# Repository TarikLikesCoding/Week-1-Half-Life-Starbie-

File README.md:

# Week-1-Half-Life-Starbie
Learning PCB's through Hack Club's Half Life program, currently working on week 1.

# What is it?
The Starbie I made is a little robot pet that you can carry anywhere. It has a lithium 3.7V battery that can be recharged. The Starbie is a robot pet with visuals on it small OLED screen, and can be interacted with using the two buttons on it and by motion of the pet. I made it with the purpose of learning how to make PCB's and made it truly mine by exploring convenience features like mobility and rechargability of it.

# How does it work?
My Starbie comes with two buttons that are used to move through the menu and interact with the actual pet inside my Starbie. There is an OLED to see the Starbie reacting to my inputs and give visuals to the project. There is a XIAO ESP32 that does all the processing in a compact chip. There are other components such as MPU-6050 and DHX711 to give the Starbie features like temperature sensing and overall motion sensing. It has a battery charging module and a LiPo battery to run when the Starbie is not connected to the laptop.

# Some Pictures

Schematic

PCB

| Part | Qty | Unit | Total | Vendor | Notes |
| :--- | :---: | :---: | :---: | :--- | :--- |
| **0.96 inch OLED Display Module** with Protector Case 128x64 SSD1306 Screen Board with 4 Pins Soldered Work Great for Arduin | 1 | $5.60 | $5.60 | Amazon | The screen that shows my starbie |
| **10PCS Blue Mechanical Keyboard Switches**, 3 Pin Clickers for Gaming | 4 | $0.48 | $1.92 | Amazon | The buttons on my starbie |
| **TP4056 Type-c USB 5V 1A 18650 Lithium Battery Charger Module** Charging Board with Dual Protection Functions 3PCS | 1 | $6.66 | $6.66 | Amazon | The charging of my LiPo battery |
| **Chanzon SPDT Mini Micro Slide Switch** 1p2t 2 Position 20pcs 3mm Toggle Vertical Slide Switch Panel Mount Small High Knob | 2 | $0.25 | $0.50 | Amazon | The switch to turn on/off the battery when the project is connected to my computer |
| **EEMB 3.7V Li-ion 502030 Battery** 250mAh Lipo Battery Rechargeable Lithium Polymer ion Battery Pack with JST Connector. | 1 | $11.91 | $11.91 | Amazon | The battery thats going to be running my starbie even without my laptop |
| **MiiEIAOD XIAO ESP32C3 Mini IoT Board** with High-Performance Cost-Effective Wi-Fi/Ble (1PCS Kit)MiiEIAOD XIAO ESP32C3 Min | 1 | $10.10 | $10.10 | Amazon | The actual brain behind my starbie |
| **PCB** | 1 | $20.55 | $20.55 | JLCPCB | The skeleton of what I will be building on |
| **Tax & shipping** | - | - | $7.44 | - | For the whole order |

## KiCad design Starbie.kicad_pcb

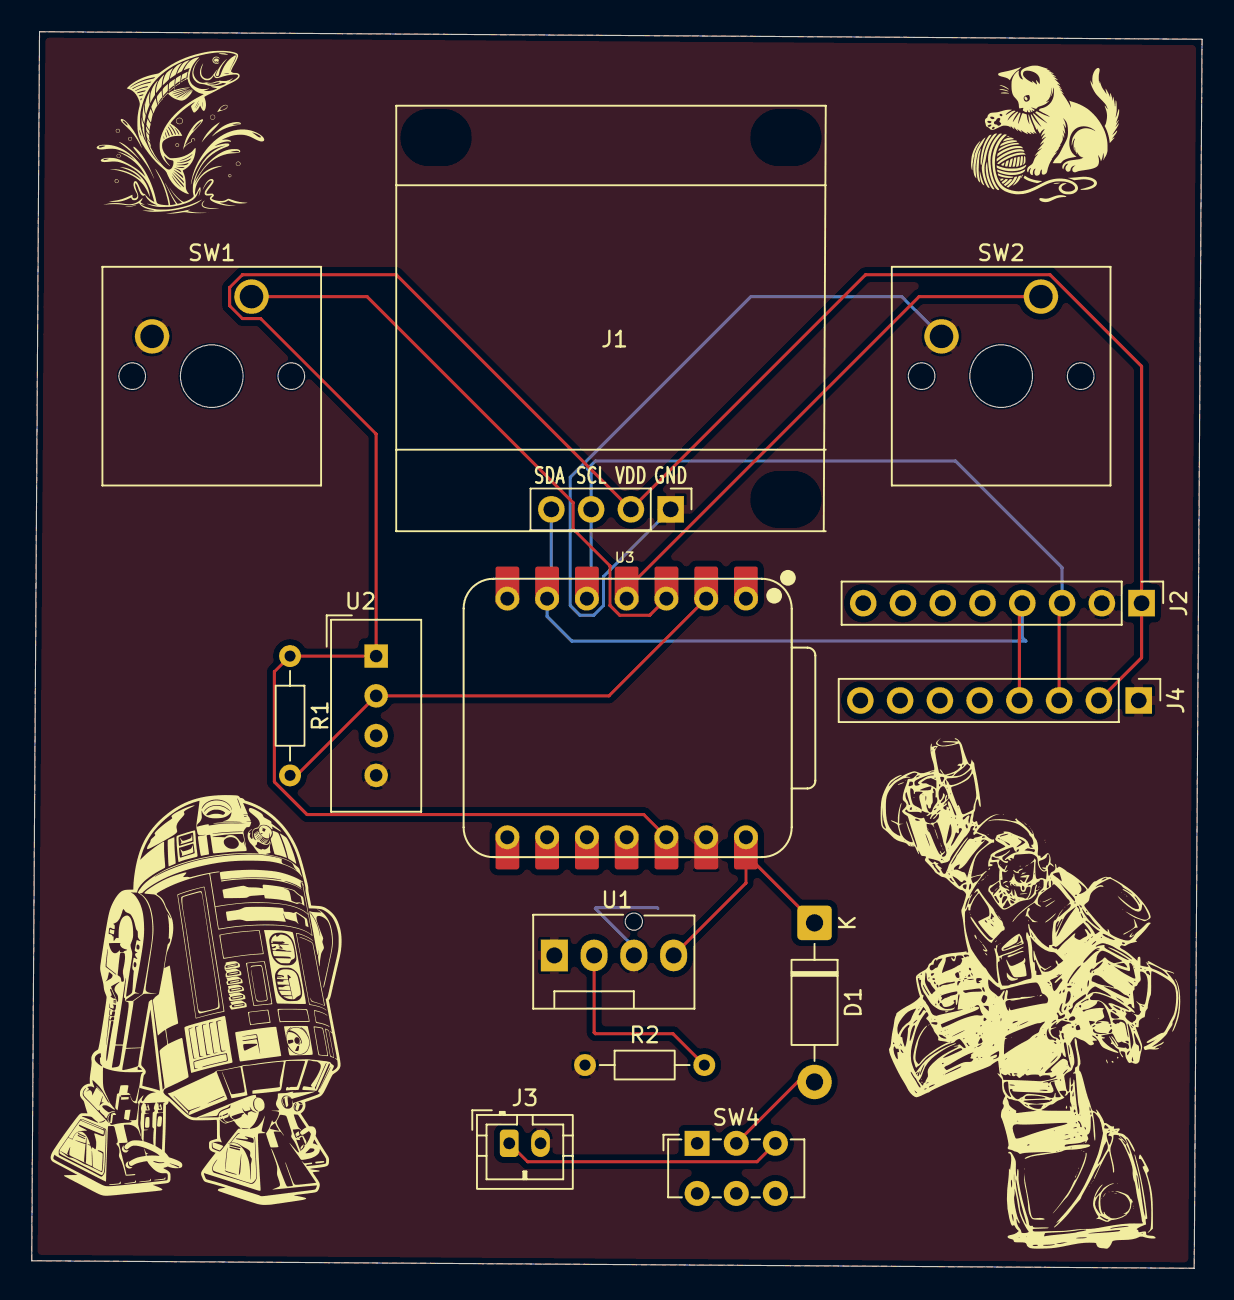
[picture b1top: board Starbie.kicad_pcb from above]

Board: 2 copper layers, 74.8 x 79.0 mm, 13 parts (0 on the bottom side), 11 nets.

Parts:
D1: 1N5819; D_DO-41_SOD81_P10.16mm_Horizontal
J1: Conn_01x04_Pin; Display_128x64_096_I2C
J2: Conn_01x08_Pin; PinHeader_1x08_P2.54mm_Vertical
J3: Conn_01x02_Socket; JST_PH_B2B-PH-K_1x02_P2.00mm_Vertical
J4: Conn_01x04_Pin; PinHeader_1x08_P2.54mm_Vertical
R1: 10k; R_Axial_DIN0204_L3.6mm_D1.6mm_P7.62mm_Horizontal
R2: 2K; R_Axial_DIN0204_L3.6mm_D1.6mm_P7.62mm_Horizontal
SW1, SW2: SW_Push; SW_Cherry_MX_1.00u_PCB
SW4: SW_SPDT; SW_E-Switch_EG1271_SPDT
U1: TP4056-42-ESOP8; FanPinHeader_1x04_P2.54mm_Vertical
U2: DHT11; Aosong_DHT11_5.5x12.0_P2.54mm
U3: XIAO-ESP32-C3-SMD; XIAO-ESP32-C6-DIP

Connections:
+3.3V: J1.2, J2.1, J4.2, R1.1, U2.1 (VDD), U3.12 (3V3_OUT)
+5V: D1.1 (K), U1.4 (V_{CC}), U3.14 (VBUS)
/(+): J3.1, SW4.3 (C)
/DHT11 DATA: R1.2, U2.2 (DATA), U3.2 (D1)
/GPIO2: SW1.1, U3.3 (D2)
/GPIO3: SW2.1, U3.4 (D3)
/SCL: J1.3, J2.3, J4.3, U3.5 (D4)
/SDA: J1.4, J2.4, J4.4, U3.6 (D5)
GND: J1.1, J2.2, J3.2, J4.1, R2.1, SW1.2, SW2.2, U1.1 (TEMP), U1.3 (GND), U2.4 (GND), U3.13 (GND)
unnamed: D1.2 (A), SW4.2 (B)
unnamed: R2.2, U1.2 (PROG)
